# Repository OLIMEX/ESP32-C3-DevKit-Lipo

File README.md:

# ESP32-C3-DevKit-Lipo
ESP32-C3-DevKit-Lipo RISC-V development board with USB, JTAG, WIFI, BT5, LiPo battery charger

Product page: https://www.olimex.com/Products/IoT/ESP32-C3/ESP32-C3-DevKit-Lipo/open-source-hardware

## License
* Hardware is released under CERN Open Hardware Licence Version 2 - Strongly Reciprocal https://spdx.org/licenses/CERN-OHL-S-2.0.html
* Software is released under GPL3 License
* Documentation is released under CC BY-SA 3.0 https://creativecommons.org/licenses/by-sa/3.0/

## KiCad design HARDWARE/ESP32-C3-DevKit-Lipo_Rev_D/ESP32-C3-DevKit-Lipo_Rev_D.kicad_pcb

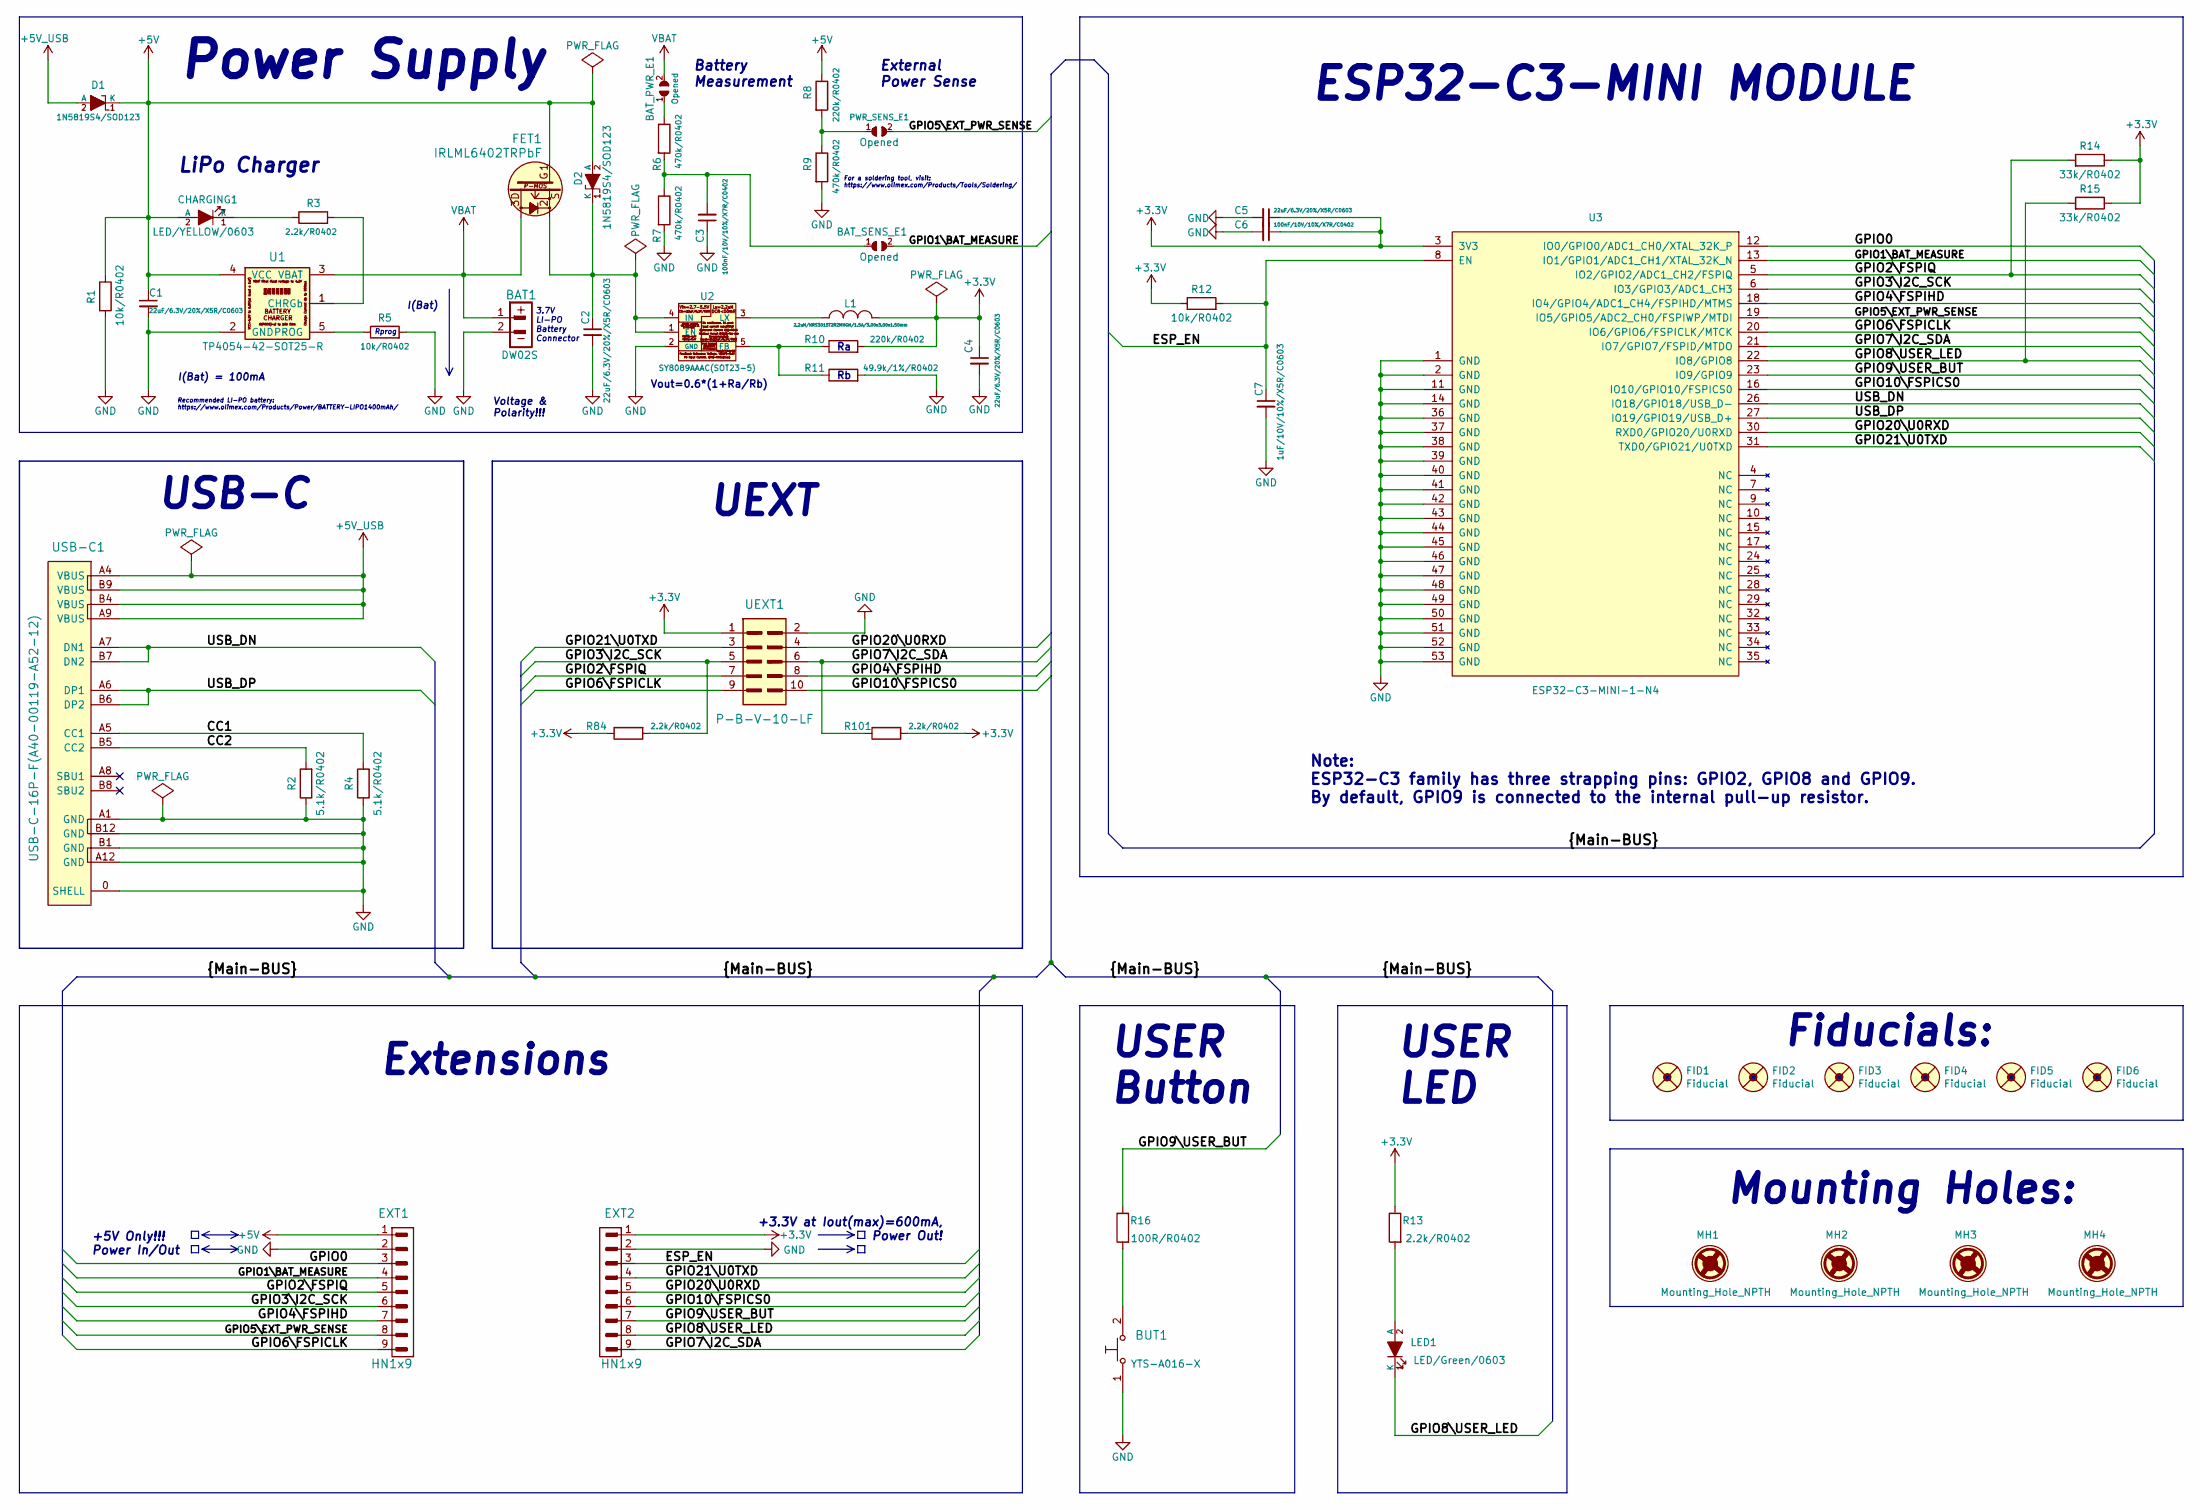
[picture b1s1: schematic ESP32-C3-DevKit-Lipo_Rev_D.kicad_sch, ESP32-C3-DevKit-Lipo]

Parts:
BAT1: DW02S; LIPO_BAT_VERTICAL_DW02S
BAT_PWR_E1: Opened; SJ_1_SMALLER
BAT_SENS_E1: Opened; SJ_1_SMALLER
BUT1: YTS-A016-X
C1, C2, C4, C5: 22uF/6.3V/20%/X5R/C0603; C_0603_5MIL_DWS
C3, C6: 100nF/10V/10%/X7R/C0402; C_0402_5MIL_DWS
C7: 1uF/10V/10%/X5R/C0603; C_0603_5MIL_DWS
CHARGING1: LED/YELLOW/0603; LED_0603_KA
D1, D2: 1N5819S4/SOD123; SOD-123_1C-2A_KA
EXT1, EXT2: HN1x9
FET1: IRLML6402TRPbF; SOT23
FID1, FID3, FID4, FID6: Fiducial; Fiducial1x3
FID2, FID5: Fiducial; Fiducial1x3_Paste
L1: 2.2uH/NRS3015T2R2MNGH/1.5A/3.00x3.00x1.50mm; CD32
LED1: LED/Green/0603; LED_0603_KA
MH1, MH2, MH3, MH4: Mounting_Hole_NPTH; Mounting_Hole_Drill-3.3mm_Clerance-7mm
PWR_SENS_E1: Opened; SJ_1_SMALLER
R1, R5, R12: 10k/R0402; R_0402_5MIL_DWS
R2, R4: 5.1k/R0402; R_0402_5MIL_DWS
R3, R13, R84, R101: 2.2k/R0402; R_0402_5MIL_DWS
R6, R7, R9: 470k/R0402; R_0402_5MIL_DWS
R8, R10: 220k/R0402; R_0402_5MIL_DWS
R11: 49.9k/1%/R0402; R_0402_5MIL_DWS
R14, R15: 33k/R0402; R_0402_5MIL_DWS
R16: 100R/R0402; R_0402_5MIL_DWS
U1: TP4054-42-SOT25-R; SOT-23-5
U2: SY8089AAAC(SOT23-5); SOT-23-5
U3: ESP32-C3-MINI-1-N4; ESP32-­C3-­MINI­-1
UEXT1: P-B-V-10-LF; GBH-254-SMT-10
USB-C1: USB-C-16P-F(A40-00119-A52-12); USB2.0_TYPE-C(A40-00119-A52-12)

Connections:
+3.3V: C4.1, C5.1, C6.1, EXT2.1, L1.2, R10.2, R12.1, R13.1, R14.1, R15.1, U3.3 (3V3), UEXT1.1; also elsewhere on the board
+5V: C1.1, CHARGING1.2 (A), D1.1 (K), D2.2 (A), EXT1.1, FET1.1, R1.1, R8.1, U1.4 (VCC)
+5V_USB: D1.2 (A), USB-C1.A4 (VBUS), USB-C1.A9 (VBUS), USB-C1.B4 (VBUS), USB-C1.B9 (VBUS)
/CC1: R4.2, USB-C1.A5 (CC1)
/CC2: R2.2, USB-C1.B5 (CC2)
/ESP_EN: C7.1, EXT2.3, R12.2, U3.8 (EN)
/GPIO0: EXT1.3, U3.12 (IO0/GPIO0/ADC1_CH0/XTAL_32K_P)
/GPIO1\BAT_MEASURE: BAT_SENS_E1.2, EXT1.4, U3.13 (IO1/GPIO1/ADC1_CH1/XTAL_32K_N)
/GPIO2\FSPIQ: EXT1.5, R14.2, U3.5 (IO2/GPIO2/ADC1_CH2/FSPIQ), UEXT1.7
/GPIO3\I2C_SCK: EXT1.6, U3.6 (IO3/GPIO3/ADC1_CH3), UEXT1.5; also elsewhere on the board
/GPIO4\FSPIHD: EXT1.7, U3.18 (IO4/GPIO4/ADC1_CH4/FSPIHD/MTMS), UEXT1.8
/GPIO5\EXT_PWR_SENSE: EXT1.8, PWR_SENS_E1.2, U3.19 (IO5/GPIO5/ADC2_CH0/FSPIWP/MTDI)
/GPIO6\FSPICLK: EXT1.9, U3.20 (IO6/GPIO6/FSPICLK/MTCK), UEXT1.9
/GPIO7\I2C_SDA: EXT2.9, U3.21 (IO7/GPIO7/FSPID/MTDO), UEXT1.6; also elsewhere on the board
/GPIO8\USER_LED: EXT2.8, LED1.1 (K), R15.2, U3.22 (IO8/GPIO8)
/GPIO9\USER_BUT: EXT2.7, R16.1, U3.23 (IO9/GPIO9)
/GPIO10\FSPICS0: EXT2.6, U3.16 (IO10/GPIO10/FSPICS0), UEXT1.10
/GPIO20\U0RXD: EXT2.5, U3.30 (RXD0/GPIO20/U0RXD), UEXT1.4
/GPIO21\U0TXD: EXT2.4, U3.31 (TXD0/GPIO21/U0TXD), UEXT1.3
/USB_DN: U3.26 (IO18/GPIO18/USB_D-), USB-C1.A7 (DN1), USB-C1.B7 (DN2)
/USB_DP: U3.27 (IO19/GPIO19/USB_D+), USB-C1.A6 (DP1), USB-C1.B6 (DP2)
GND: BAT1.2, BUT1.1, C1.2, C2.2, C3.1, C4.2, C5.2, C6.2, C7.2, EXT1.2, EXT2.2, R1.2, R2.1, R4.1, R5.2, R7.2, R9.2, R11.2, U1.2 (GND), U2.2 (GND), U3.1 (GND), U3.2 (GND), U3.11 (GND), U3.14 (GND), U3.36 (GND), U3.37 (GND), U3.38 (GND), U3.39 (GND), U3.40 (GND), U3.41 (GND), U3.42 (GND), U3.43 (GND), U3.44 (GND), U3.45 (GND), U3.46 (GND), U3.47 (GND), U3.48 (GND), U3.49 (GND), U3.50 (GND), U3.51 (GND), U3.52 (GND), U3.53 (GND), UEXT1.2, USB-C1.0 (SHELL), USB-C1.A1 (GND), USB-C1.A12 (GND), USB-C1.B1 (GND), USB-C1.B12 (GND)
unnamed: BAT_PWR_E1.1, R6.1
unnamed: BAT_SENS_E1.1, C3.2, R6.2, R7.1
unnamed: BUT1.2, R16.2
unnamed: CHARGING1.1 (K), R3.1
unnamed: C2.1, D2.1 (K), FET1.2, U2.1 (EN), U2.4 (IN)
unnamed: LED1.2 (A), R13.2
unnamed: PWR_SENS_E1.1, R8.2, R9.1
unnamed: R3.2, U1.1 (CHRGb)
unnamed: R5.1, U1.5 (PROG)
unnamed: R10.1, R11.1, U2.5 (FB)
unnamed: L1.1, U2.3 (LX)
VBAT: BAT1.1, BAT_PWR_E1.2, FET1.3, U1.3 (VBAT)

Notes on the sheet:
USER Button
Mounting Holes:
Note: ESP32-C3 family has three strapping pins: GPIO2, GPIO8 and GPIO9. By default, GPIO9 is connected to the internal pull-up resistor.
Recommended LI-PO battery: https://www.olimex.com/Products/Power/BATTERY-LIPO1400mAh/
ESP32-C3-MINI MODULE
Voltage & Polarity!!!
3.7V LI-PO Battery Connector
Vout=0.6*(1+Ra/Rb)
+3.3V at Iout(max)=600mA, Power Out!
LiPo Charger
USER LED
Extensions
Battery Measurement
+5V Only!!! Power In/Out
For a soldering tool, visit: https://www.olimex.com/Products/Tools/Soldering/
UEXT
External Power Sense
I(Bat) = 100mA
USB-C
Power Supply
Fiducials:
I(Bat)
Rprog

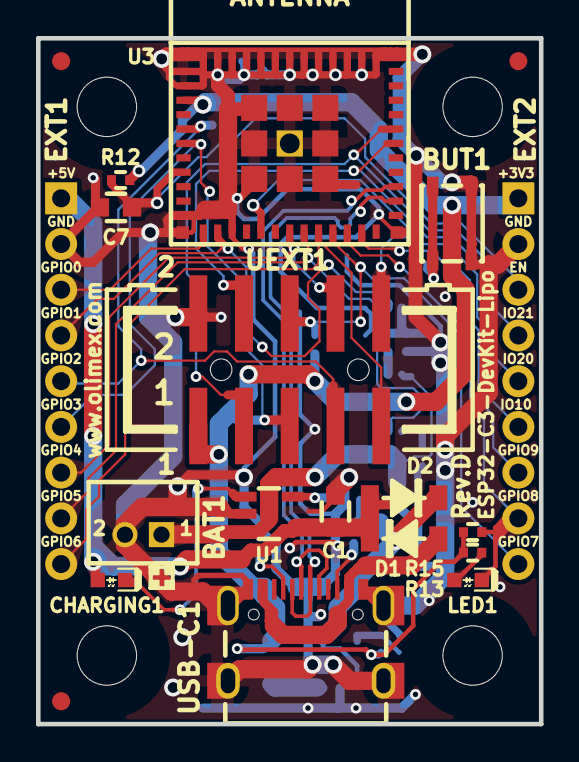
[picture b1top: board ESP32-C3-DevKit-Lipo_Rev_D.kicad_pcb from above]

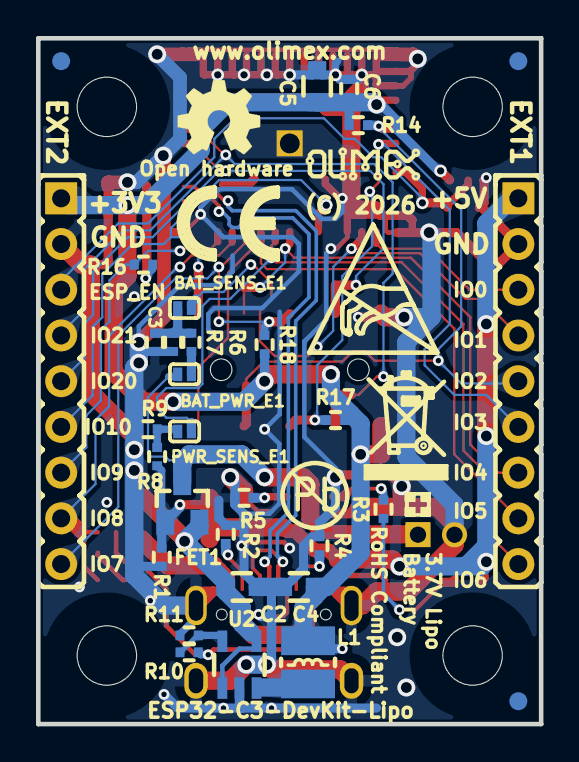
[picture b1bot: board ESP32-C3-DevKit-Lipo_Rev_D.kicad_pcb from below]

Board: 2 copper layers, 27.9 x 38.1 mm, 59 parts (37 on the bottom side), 34 nets.

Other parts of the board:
Logo_OLIMEX_2: Logo_OLIMEX_2; Logo_OLIMEX_80
R17, R18: 2.2k/R0402; R_0402_5MIL_DWS
Sign_Antistatic: Sign_Antistatic
Sign_CE: CE_Sign
Sign_OSHW_7.3x6.0mm: Sign_OSHW_7.3x6.0mm; Sign_OSHW_7.3x6.0mmn
Sign_PB-Free: Sign_PB-Free
Sign_RecycleBin_1: Sign_RecycleBin_1

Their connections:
+3.3V: R17.1, R18.2; also elsewhere on the board
/GPIO3\I2C_SCK: R17.2; also elsewhere on the board
/GPIO7\I2C_SDA: R18.1; also elsewhere on the board

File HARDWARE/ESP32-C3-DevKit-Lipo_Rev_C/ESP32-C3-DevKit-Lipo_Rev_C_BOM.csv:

"Id";"Designator";"Footprint";"Quantity";"Designation";"Supplier and ref";
1;"FID1,FID3,FID4,FID6";"Fiducial1x3";4;"Fiducial";;;
2;"C1,C2,C5,C4";"C_0603_5MIL_DWS";4;"22uF/6.3V/20%/X5R/C0603";;;
3;"R12,R1,R5";"R_0402_5MIL_DWS";3;"10k/R0402";;;
4;"R13,R3,R18,R17";"R_0402_5MIL_DWS";4;"2.2k/R0402";;;
5;"D2,D1";"SOD-123_1C-2A_KA";2;"1N5819S4/SOD123";;;
6;"BAT1";"LIPO_BAT_VERTICAL_DW02S";1;"DW02S";;;
7;"R15,R14";"R_0402_5MIL_DWS";2;"33k/R0402";;;
8;"FID2,FID5";"Fiducial1x3_Paste";2;"Fiducial";;;
9;"LED1";"LED_0603_KA";1;"LED/Green/0603";;;
10;"MH1,MH2,MH3,MH4";"Mounting_Hole_Drill-3.3mm_Clerance-7mm";4;"Mounting_Hole_NPTH";;;
11;"U3";"ESP32-­C3-­MINI­-1";1;"ESP32-C3-MINI-1-N4";;;
12;"CHARGING1";"LED_0603_KA";1;"LED/YELLOW/0603";;;
13;"BUT1";"YTS-A016-X";1;"YTS-A016-X";;;
14;"U1";"SOT-23-5";1;"TP4054-42-SOT25-R";;;
15;"C7";"C_0603_5MIL_DWS";1;"1uF/10V/10%/X5R/C0603";;;
16;"USB-C1";"USB2.0_TYPE-C(A40-00119-A52-12)";1;"USB-C-16P-F(A40-00119-A52-12)";;;
17;"UEXT1";"GBH-254-SMT-10";1;"P-B-V-10-LF";;;
18;"BAT_PWR_E1,BAT_SENS_E1,PWR_SENS_E1";"SJ_1_SMALLER";3;"Opened";;;
19;"R6,R7,R9";"R_0402_5MIL_DWS";3;"470k/R0402";;;
20;"R8,R10";"R_0402_5MIL_DWS";2;"220k/R0402";;;
21;"L1";"CD32";1;"2.2uH/NRS3015T2R2MNGH/1.5A/3.00x3.00x1.50mm";;;
22;"R11";"R_0402_5MIL_DWS";1;"49.9k/1%/R0402";;;
23;"C3,C6";"C_0402_5MIL_DWS";2;"100nF/10V/10%/X7R/C0402";;;
24;"FET1";"SOT23";1;"IRLML6402TRPbF";;;
25;"EXT1,EXT2";"HN1x9";2;"HN1x9";;;
26;"R2,R4";"R_0402_5MIL_DWS";2;"5.1k/R0402";;;
27;"U2";"SOT-23-5";1;"SY8089AAAC(SOT23-5)";;;
28;"Logo_OLIMEX_2";"Logo_OLIMEX_80";1;"Logo_OLIMEX_2";;;
29;"Sign_CE";"CE_Sign";1;"CE_Sign";;;
30;"Sign_Antistatic";"Sign_Antistatic";1;"Sign_Antistatic";;;
31;"Sign_PB-Free";"Sign_PB-Free";1;"Sign_PB-Free";;;
32;"Sign_RecycleBin_1";"Sign_RecycleBin_1";1;"Sign_RecycleBin_1";;;
33;"R16";"R_0402_5MIL_DWS";1;"100R/R0402";;;

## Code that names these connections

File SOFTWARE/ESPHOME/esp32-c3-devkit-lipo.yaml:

esphome:
  name: esp32-c3-devkit-lipo
  comment: Olimex ESP32-C3-DevKit-LiPo (native USB, LiPo, UEXT)

esp32:
  board: esp32-c3-devkitm-1
  framework:
    type: arduino

# ================= CORE =================

logger:
  hardware_uart: USB_CDC

api:

ota:
  - platform: esphome

# ================= WIFI =================

wifi:
  ssid: !secret wifi_ssid
  password: !secret wifi_password

  ap:
    ssid: "ESP32-C3-LiPo Fallback"
    password: "fallback123"

captive_portal:

# ================= ONBOARD LED =================

output:
  - platform: gpio
    id: led_green_out
    pin:
      number: GPIO8
      mode: OUTPUT
      inverted: false

light:
  - platform: binary
    name: "Onboard LED"
    output: led_green_out

# ================= USER BUTTON =================

binary_sensor:
  - platform: gpio
    name: "User Button"
    pin:
      number: GPIO9
      mode: INPUT_PULLUP
      inverted: true
    filters:
      - delayed_on: 10ms
      - delayed_off: 10ms

# GPIO9 is a boot strapping pin.
# Holding the button during reset may prevent boot.

# ================= OPTIONAL (REQUIRES JUMPERS) =================

# ---- External Power Sense (GPIO5) ----
# Requires hardware jumper to be CLOSED
#
#binary_sensor:
#  - platform: gpio
#    name: "External Power Present"
#    pin:
#      number: GPIO5
#      mode: INPUT

# ---- Battery Voltage (GPIO1 via divider) ----
# Requires hardware jumper to be CLOSED
# Divider: 470k / 470k → multiply by 2
#
#sensor:
#  - platform: adc
#    pin: GPIO1
#    name: "Battery Voltage"
#    attenuation: 12db
#    update_interval: 10s
#    filters:
#      - multiply: 2.0

# ================= UEXT =================

uart:
  - id: uext_uart
    tx_pin: GPIO21
    rx_pin: GPIO20
    baud_rate: 115200

i2c:
  - id: uext_i2c
    scl: GPIO3
    sda: GPIO7
    scan: true

spi:
  - id: uext_spi
    clk_pin: GPIO6
    mosi_pin: GPIO10
    miso_pin: GPIO2

# ================= NOTES =================
#
# GPIO1 (ADC) and GPIO5 are NOT available unless
# corresponding board jumpers are populated.
#
# This config keeps default firmware safe for
# out-of-the-box hardware state.
#
# Enable those sections only after closing jumpers.
#
# Avoid using GPIO4 (FSPIHD) unless you know exactly
# what you're doing with SPI flash modes.

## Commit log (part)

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2022-10-06 inisital commit
2022-10-07 add user manual
2024-04-05 Create ESP32-C3-DevKit-Lipo-dimensions.pdf
    Added dimensions
2026-03-20 Update
    New hardware revision C
2026-04-17 Update
    Simple demo
2026-04-24 Update
    added esphome and platformio configuration files
2026-06-11 add telegram home automation example
2026-06-11 Update project description in telegram.ino
    Added project description link for home automation.
